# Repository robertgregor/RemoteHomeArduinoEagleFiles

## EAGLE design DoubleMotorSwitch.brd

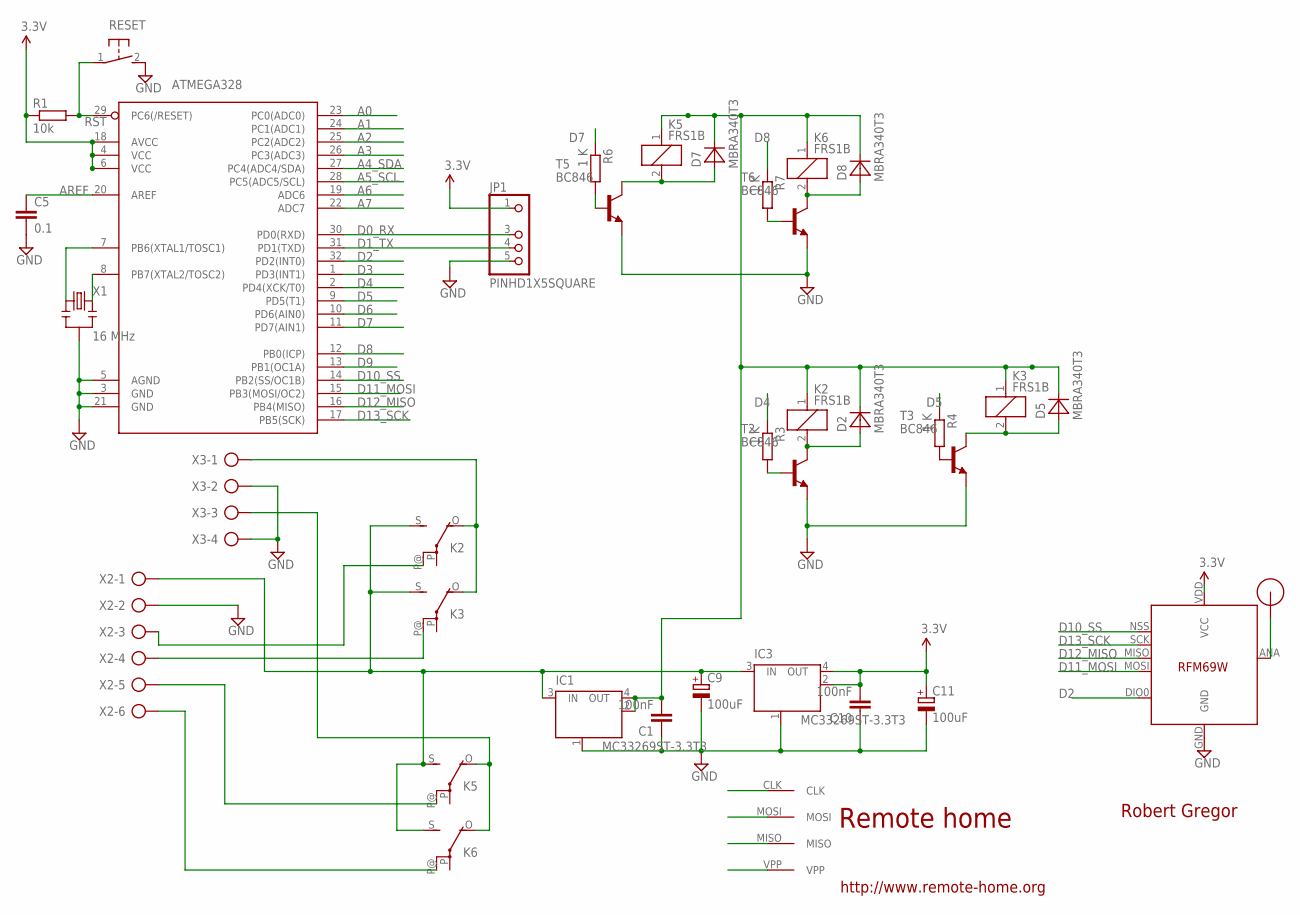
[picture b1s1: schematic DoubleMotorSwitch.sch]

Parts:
ATMEGA328: ATMega-328; TQFP32-08
C1, C10: 100nF; C2012
C5: 0.1; C2012
C9, C11: 100uF; SMC_B
D2, D5, D7, D8: MBRA340T3; SMA
IC1, IC3: MC33269ST-3.3T3; SOT223
JP1: PINHD1X5SQUARE; PINHD1X05-SQUARE
K2, K3, K5, K6: FRS1B
R1: 10k; R2012
R3, R4, R6, R7: 1 K; M2012
RESET: DTSM-3
T2, T3, T5, T6: BC846; SOT23
U$1: RFM12B_ANTENNA; RFM12B-ANTENNA
U$2: AVRHEADERDIP; AVRHEADER
U$5: RFM69; RFM69W-MINPADS
X1: 16 MHz; RESONATOR-SMD
X2: AK500/6
X3: AK500/4

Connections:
5V1: C1.2, D2.C, D5.C, D7.C, D8.C, IC1.2 (OUT), IC1.4 (OUT), K2.1, K3.1, K5.1, K6.1
A0: ATMEGA328.23 (PC0(ADC0))
A1: ATMEGA328.24 (PC1(ADC1))
A2: ATMEGA328.25 (PC2(ADC2))
A3: ATMEGA328.26 (PC3(ADC3))
A4_SDA: ATMEGA328.27 (PC4(ADC4/SDA))
A5_SCL: ATMEGA328.28 (PC5(ADC5/SCL))
A6: ATMEGA328.19 (ADC6)
A7: ATMEGA328.22 (ADC7)
AREF: ATMEGA328.20 (AREF), C5.1
D0_RX: ATMEGA328.30 (PD0(RXD)), JP1.3
D1_TX: ATMEGA328.31 (PD1(TXD)), JP1.4
D2: ATMEGA328.32 (PD2(INT0)), U$5.DIO0
D3: ATMEGA328.1 (PD3(INT1))
D4: ATMEGA328.2 (PD4(XCK/T0)), R3.1
D5: ATMEGA328.9 (PD5(T1)), R4.1
D6: ATMEGA328.10 (PD6(AIN0))
D7: ATMEGA328.11 (PD7(AIN1)), R6.1
D8: ATMEGA328.12 (PB0(ICP)), R7.1
D9: ATMEGA328.13 (PB1(OC1A))
D10_SS: ATMEGA328.14 (PB2(SS/OC1B)), U$5.NSS (SEL)
D11_MOSI: ATMEGA328.15 (PB3(MOSI/OC2)), U$2.MOSI, U$5.MOSI
D12_MISO: ATMEGA328.16 (PB4(MISO)), U$2.MISO, U$5.MISO
D13_SCK: ATMEGA328.17 (PB5(SCK)), U$2.CLK, U$5.SCK
GND: ATMEGA328.3 (GND), ATMEGA328.5 (AGND), ATMEGA328.21 (GND), C1.1, C5.2, C9.-, C10.1, C11.-, IC1.1 (GND/ADJ), IC3.1 (GND/ADJ), JP1.5, RESET.2, T2.2 (E), T3.2 (E), T5.2 (E), T6.2 (E), U$5.GND, X1.2, X2.2, X3.2, X3.4
unnamed: ATMEGA328.7 (PB6(XTAL1/TOSC1)), X1.1
unnamed: U$1.P$1, U$5.ANA (ANT)
unnamed: D2.A, K2.2, T2.3 (C)
unnamed: R3.2, T2.1 (B)
unnamed: K2.P@, X2.3
unnamed: K2.O, K3.O, X3.1
unnamed: K3.P@, X2.4
unnamed: K5.O, K6.O, X3.3
unnamed: C9.+, IC1.3 (IN), IC3.3 (IN), K2.S, K3.S, K5.S, K6.S, X2.1
unnamed: K5.P@, X2.5
unnamed: K6.P@, X2.6
unnamed: ATMEGA328.8 (PB7(XTAL2/TOSC2)), X1.3
unnamed: D5.A, K3.2, T3.3 (C)
unnamed: R4.2, T3.1 (B)
unnamed: D7.A, K5.2, T5.3 (C)
unnamed: R6.2, T5.1 (B)
unnamed: D8.A, K6.2, T6.3 (C)
unnamed: R7.2, T6.1 (B)
RST: ATMEGA328.29 (PC6(/RESET)), R1.2, RESET.1, U$2.VPP
VCC: ATMEGA328.4 (VCC), ATMEGA328.6 (VCC), ATMEGA328.18 (AVCC), C10.2, C11.+, IC3.2 (OUT), IC3.4 (OUT), JP1.1, R1.1, U$5.VDD (VCC)

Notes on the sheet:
Remote home
Robert Gregor
http://www.remote-home.org

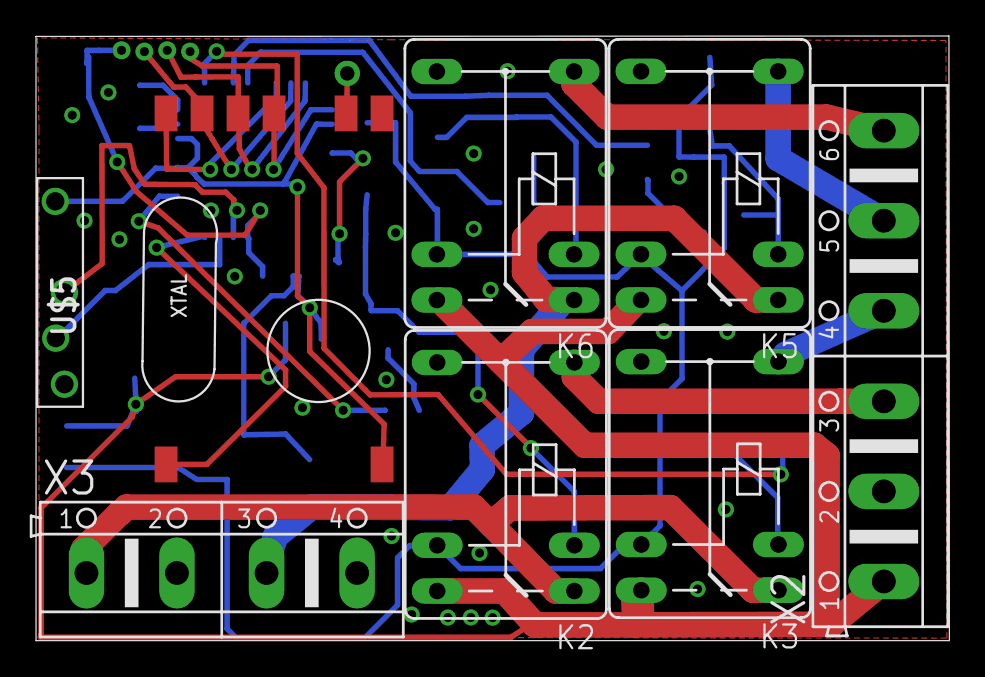
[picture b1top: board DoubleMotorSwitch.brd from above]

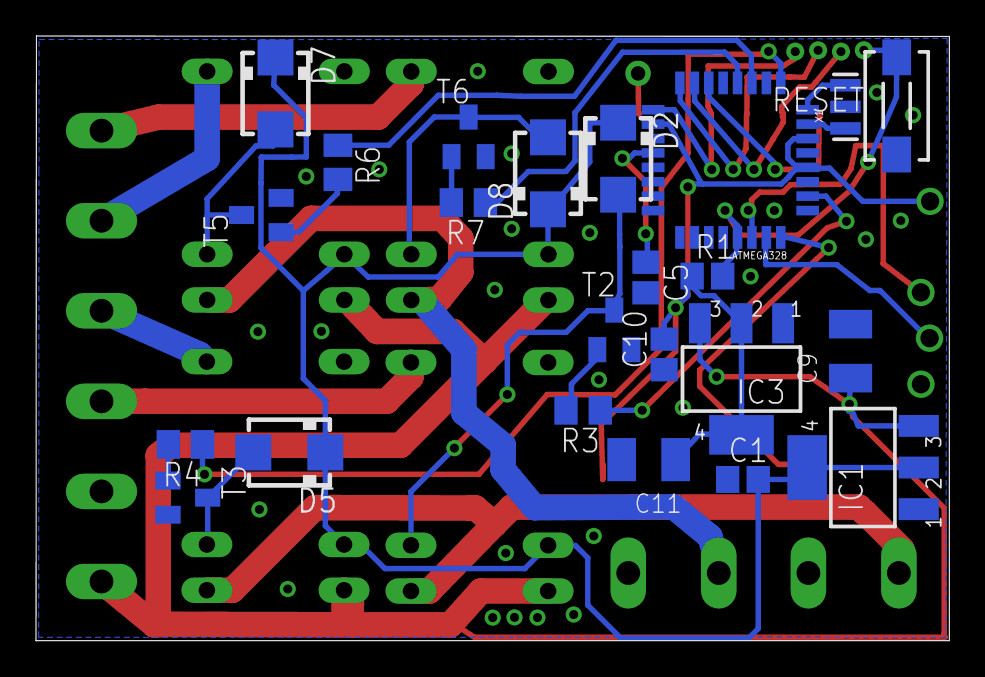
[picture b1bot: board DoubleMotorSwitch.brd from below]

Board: 2 copper layers, 50.7 x 33.6 mm, 33 parts (23 on the bottom side), 34 nets.

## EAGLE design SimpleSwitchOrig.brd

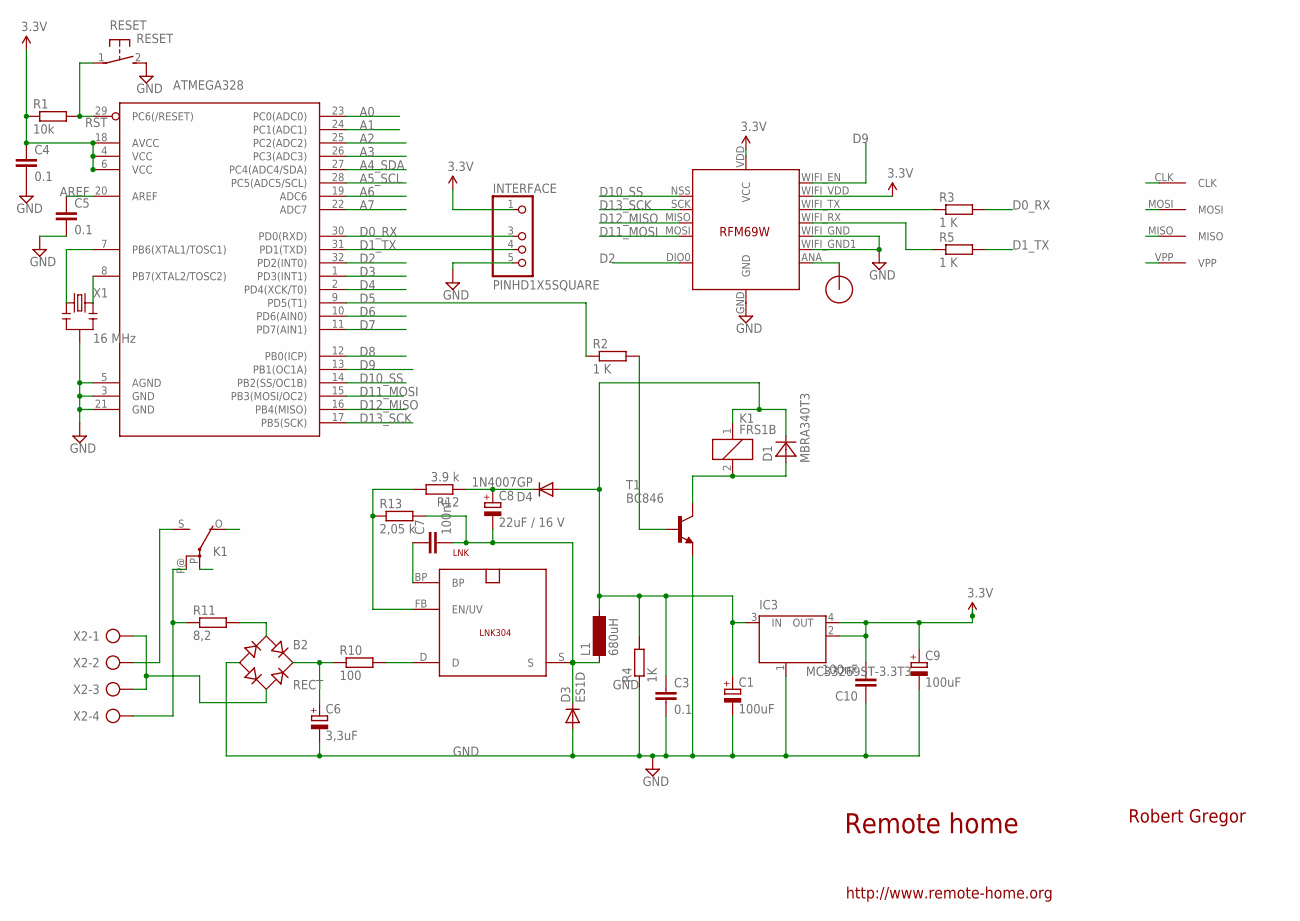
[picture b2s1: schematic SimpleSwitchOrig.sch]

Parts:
ATMEGA328: ATMega-328; TQFP32-08
B2: RECT; TO-269AA
C1, C9: 100uF; SMC_B
C3, C4, C5: 0.1; C2012
C6: 3,3uF; E5-10,5
C7, C10: 100nF; C2012
C8: 22uF / 16 V; SMC_C
D1: MBRA340T3; SMA
D3: ES1D; DO214AC
D4: 1N4007GP; DO214AA
IC3: MC33269ST-3.3T3; SOT223
INTERFACE: PINHD1X5SQUARE; PINHD1X05-SQUARE
K1: FRS1B
L1: 680uH; BS11
LNK: LNK304; SO-8C
R1: 10k; R2012
R2, R3, R5: 1 K; M2012
R4: 1K; M2012
R10: 100; R2512W
R11: 8,2; 0411/12
R12: 3.9 k; M2012
R13: 2,05 k; M2012
RESET: RESET; DTSM-3
RFM69: RFM69-ESP03; RFM69W-ESP03
T1: BC846; SOT23
U$1: RFM12B_ANTENNA; RFM12B-ANTENNA
U$2: AVRHEADERDIP; AVRHEADER
X1: 16 MHz; RESONATOR-SMD
X2: AK500/4

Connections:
5V: C1.+, C3.1, D1.C, D4.A, IC3.3 (IN), K1.1, L1.2, R4.2
A0: ATMEGA328.23 (PC0(ADC0))
A1: ATMEGA328.24 (PC1(ADC1))
A2: ATMEGA328.25 (PC2(ADC2))
A3: ATMEGA328.26 (PC3(ADC3))
A4_SDA: ATMEGA328.27 (PC4(ADC4/SDA))
A5_SCL: ATMEGA328.28 (PC5(ADC5/SCL))
A6: ATMEGA328.19 (ADC6)
A7: ATMEGA328.22 (ADC7)
AREF: ATMEGA328.20 (AREF), C5.1
D0_RX: ATMEGA328.30 (PD0(RXD)), INTERFACE.3, R3.2
D1_TX: ATMEGA328.31 (PD1(TXD)), INTERFACE.4, R5.2
D2: ATMEGA328.32 (PD2(INT0)), RFM69.DIO0
D3: ATMEGA328.1 (PD3(INT1))
D4: ATMEGA328.2 (PD4(XCK/T0))
D5: ATMEGA328.9 (PD5(T1)), R2.1
D6: ATMEGA328.10 (PD6(AIN0))
D7: ATMEGA328.11 (PD7(AIN1))
D8: ATMEGA328.12 (PB0(ICP))
D9: ATMEGA328.13 (PB1(OC1A)), RFM69.WIFI_EN
D10_SS: ATMEGA328.14 (PB2(SS/OC1B)), RFM69.NSS (SEL)
D11_MOSI: ATMEGA328.15 (PB3(MOSI/OC2)), RFM69.MOSI, U$2.MOSI
D12_MISO: ATMEGA328.16 (PB4(MISO)), RFM69.MISO, U$2.MISO
D13_SCK: ATMEGA328.17 (PB5(SCK)), RFM69.SCK, U$2.CLK
FB: LNK.FB (EN/UV), R12.2, R13.1
GND: ATMEGA328.3 (GND), ATMEGA328.5 (AGND), ATMEGA328.21 (GND), B2.-, C1.-, C3.2, C4.2, C5.2, C6.-, C9.-, C10.1, D3.A, IC3.1 (GND/ADJ), INTERFACE.5, R4.1, RESET.2, RFM69.GND, RFM69.WIFI_GND, RFM69.WIFI_GND1, T1.2 (E), X1.2
unnamed: ATMEGA328.7 (PB6(XTAL1/TOSC1)), X1.1
unnamed: R2.2, T1.1 (B)
unnamed: RFM69.ANA (ANT), U$1.P$1
unnamed: D1.A, K1.2, T1.3 (C)
unnamed: K1.S, X2.2
unnamed: K1.P@, R11.1, X2.4
unnamed: B2.AC2, X2.1, X2.3
unnamed: R3.1, RFM69.WIFI_TX
unnamed: R5.1, RFM69.WIFI_RX
unnamed: LNK.D, R10.2
unnamed: B2.+, C6.+, R10.1
unnamed: B2.AC1, R11.2
unnamed: C7.1, LNK.BP
unnamed: C8.+, D4.C, R12.1
unnamed: ATMEGA328.8 (PB7(XTAL2/TOSC2)), X1.3
RST: ATMEGA328.29 (PC6(/RESET)), R1.2, RESET.1, U$2.VPP
S: C7.2, C8.-, D3.C, L1.1, LNK.S, R13.2
VCC: ATMEGA328.4 (VCC), ATMEGA328.6 (VCC), ATMEGA328.18 (AVCC), C4.1, C9.+, C10.2, IC3.2 (OUT), IC3.4 (OUT), INTERFACE.1, R1.1, RFM69.VDD (VCC), RFM69.WIFI_VDD

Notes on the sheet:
Remote home
Robert Gregor
http://www.remote-home.org

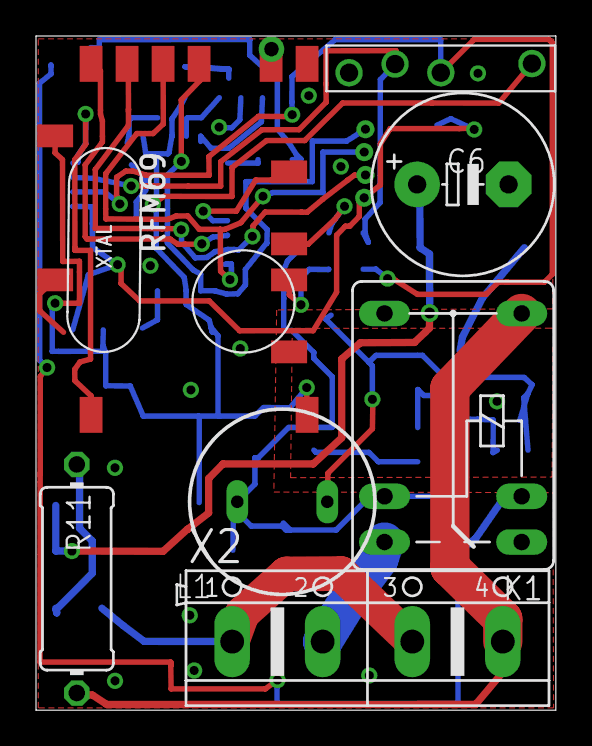
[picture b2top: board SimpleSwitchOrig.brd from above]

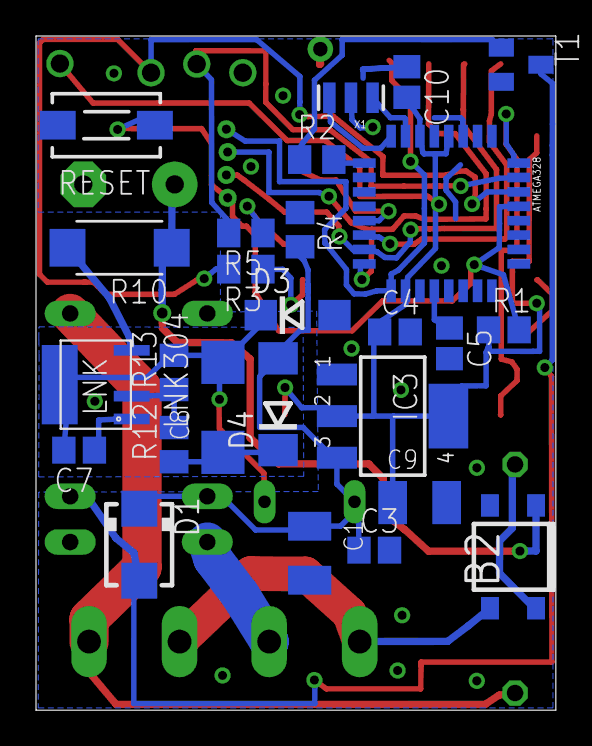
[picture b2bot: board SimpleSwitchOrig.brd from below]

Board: 2 copper layers, 28.9 x 37.5 mm, 35 parts (26 on the bottom side), 31 nets.

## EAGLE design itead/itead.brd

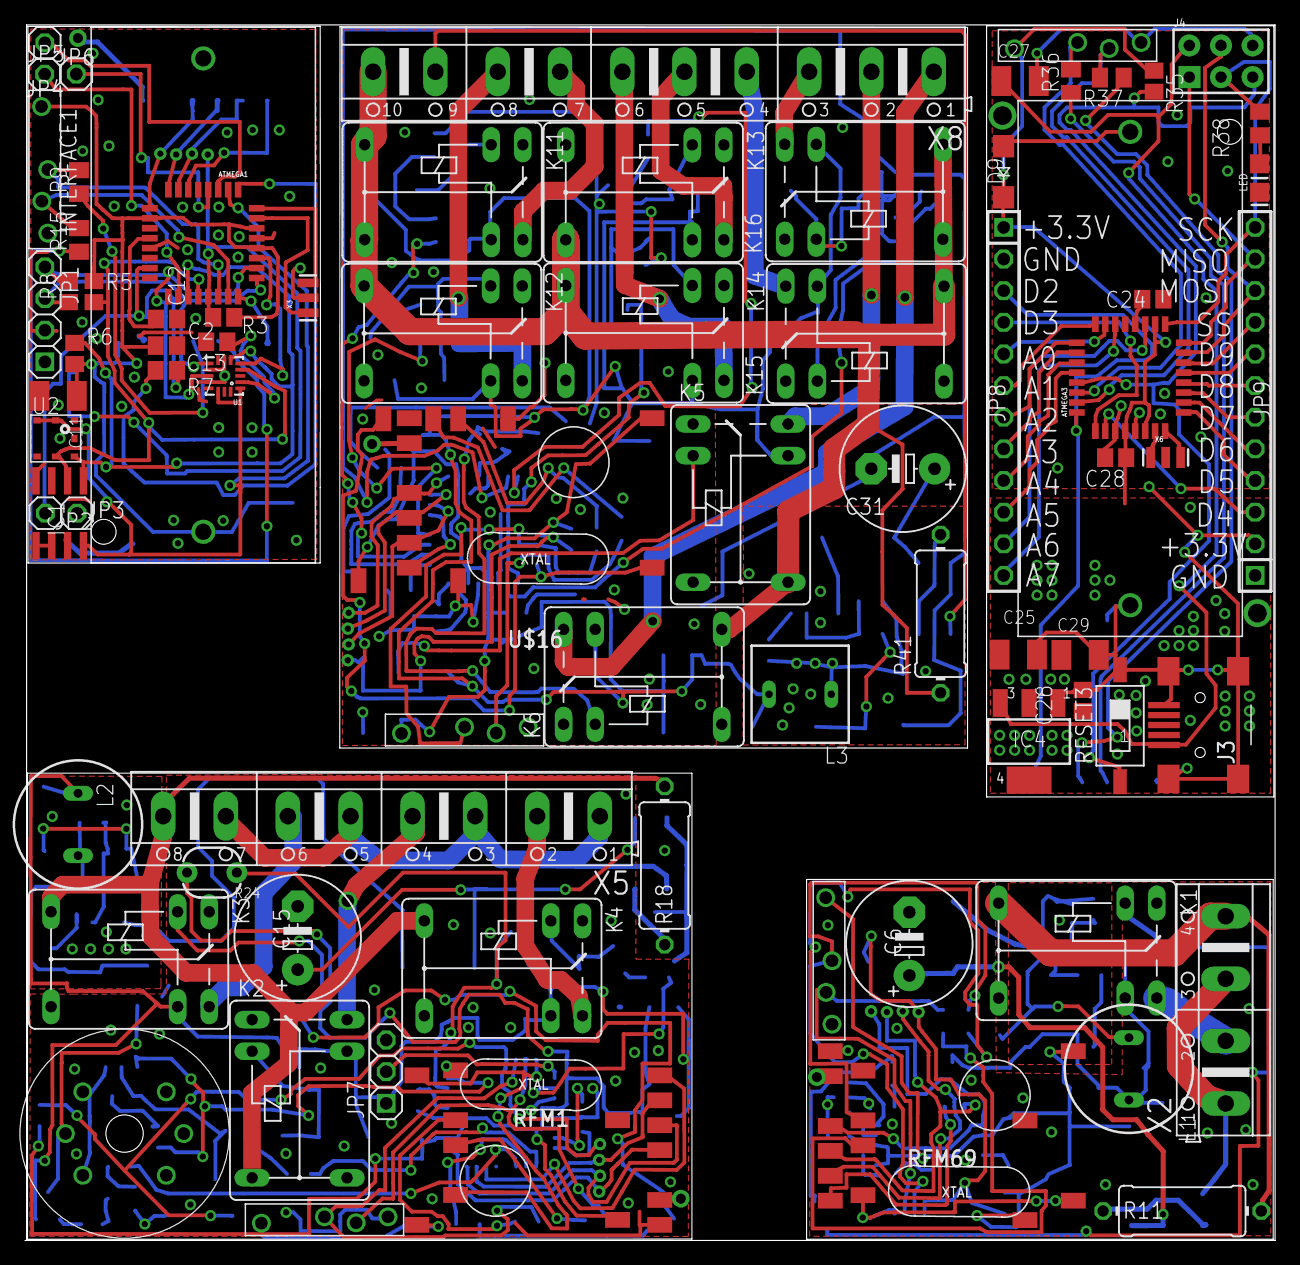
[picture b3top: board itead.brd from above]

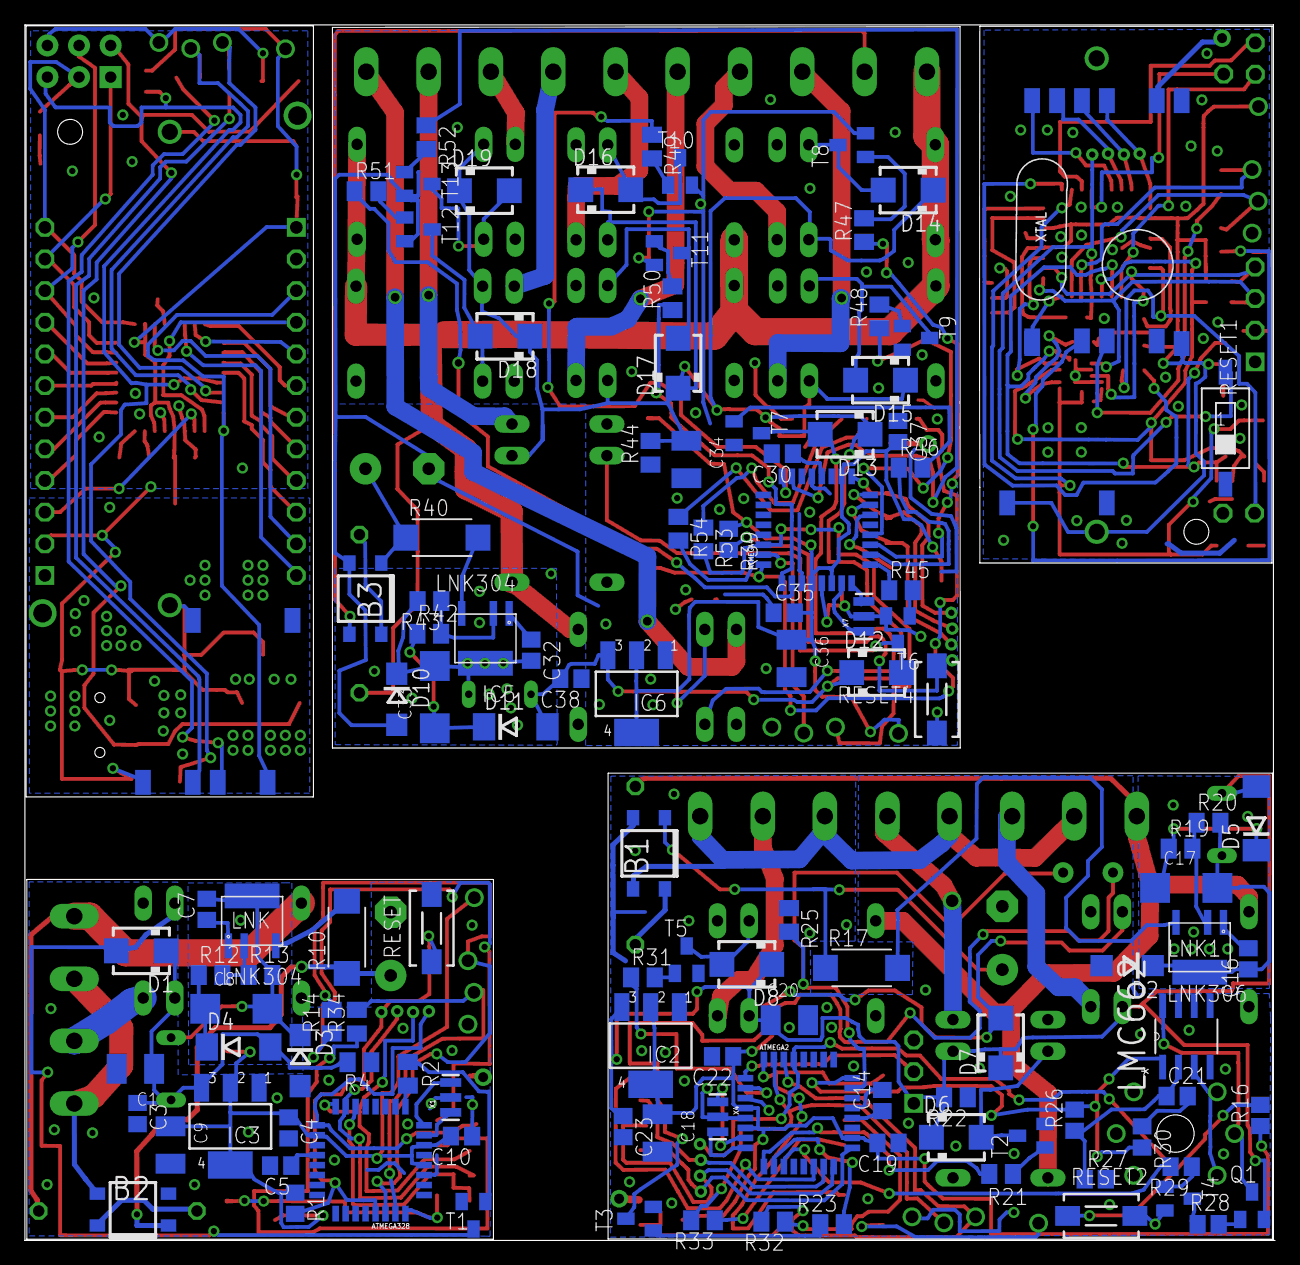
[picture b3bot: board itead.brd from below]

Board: 2 copper layers, 100.2 x 97.6 mm, 209 parts (119 on the bottom side), 197 nets.

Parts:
ATMEGA1, ATMEGA2, ATMEGA3, ATMEGA4, ATMEGA328: ATMega-328; TQFP32-08
B1, B2: RECT; TO-269AA
B3: RECTIFIER; TO-269AA
C1, C9, C11, C18, C20, C25, C27, C29, C34, C36: 100uF; SMC_B
C2, C7, C10, C13, C14, C16, C19, C21, C22, C23, C26, C32, C35, C37, C38: 100nF; C2012
C3, C4, C5, C12, C24, C28, C30: 0.1; C2012
C6, C15, C31: 3,3uF; E5-10,5
C8, C17, C33: 22uF / 16 V; SMC_C
D1, D6, D7, D8, D12, D13, D14, D15, D16, D17, D18, D19: MBRA340T3; SMA
D2, D3, D10: ES1D; DO214AC
D4, D5, D11: 1N4007GP; DO214AA
D9: GF1; SMA-DO214AC
IC1: LM75AD; SO08
IC2, IC3, IC4, IC6: MC33269ST-3.3T3; SOT223
IC5: LNK304; SO-8C
INTERFACE, INTERFACE1, INTERFACE2, INTERFACE3: PINHD1X5SQUARE; PINHD1X05-SQUARE
J3: USB-MINI-B%C; USB-MINI-B_2
J4: HEAD3X2
JP1: 1X04-S
JP2, JP3, JP4, JP5, JP6: 1X01
JP7: 1X03-S
JP8, JP9: 1X12
JP10: PINHD1X5SQUARE; PINHD1X05-SQUARE
K1, K2, K3, K4, K5, K6, K11, K12, K13, K14, K15, K16: FRS1B
L1, L2: 680uH; BS11
L3: 680uH; SD8
LED: L_AMBER; LED0805
LMC662: LMV722IDR; SOIC127P600X175-8N
LNK: LNK304; SO-8C
LNK1: LNK306; SO-8C
Q1: BC327SMD; SOT23-BEC
R1, R3, R5, R6, R7, R8, R16, R26, R28, R35, R39: 10k; R2012
R2, R9, R14, R15, R21, R23, R31, R32, R33, R34, R36, R37, R45, R46, R47, R48, R49, R50, R51, R52, R53, R54: 1 K; M2012
R4, R22, R44: 1K; M2012
R10, R17, R40: 100; R2512W
R11, R18, R41: 8,2; 0411/12
R12, R42: 3.9 k; M2012
R13, R20, R43: 2,05 k; M2012
R19: 5.1 k; M2012
R24: PHOTOCELLPTH; PHOTOCELL
R25: 10 K; M2012
R27: 2k; R2012
R29, R30: 1k; R2012
R38: 220; M2012
RESET, RESET2: RESET; DTSM-3
RESET1, RESET3: SMS-001
RESET4: DTSM-3
RFM1, RFM69: RFM69W
T1, T2, T3, T4, T5, T6, T7, T8, T9, T10, T11, T12, T13: BC846; SOT23
U1: MMA8452Q; QFN-16_0.5MM
U2: BMP180
U$1, U$3, U$8, U$15: RFM12B_ANTENNA; RFM12B-ANTENNA
U$2, U$4, U$10, U$17: AVRHEADERDIP; AVRHEADER
U$5, U$13: BATT-CR123A; KEYSTONE-2/3A
U$6: RFM69W
U$7, U$9, U$12, U$14, U$18: ESP03
U$11: METHANE_SENSOR; MQ-3
U$16: RFM69; RFM69W-MINPADS
X1, X3, X4, X6, X7: 16 MHz; RESONATOR-SMD
X2: AK500/4
X5: AK500/8
X8: AK500/10

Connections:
5V1: C27.+, IC4.3, J3.5, J4.2
5V2: C1.+, C3.1, D1.C, D4.A, IC3.3, K1.1, L1.2, R4.2
5V3: C34.+, C38.2, D11.A, D12.C, D13.C, D14.C, D15.C, D16.C, D17.C, D18.C, D19.C, IC6.3, K5.1, K6.1, K11.1, K12.1, K13.1, K14.1, K15.1, K16.1, L3.2, R44.2
6V: C20.+, C23.1, D5.A, D6.C, D7.C, D8.C, IC2.3, JP7.1, K2.1, K3.1, K4.1, L2.2, Q1.E, R22.2
A4_SDA1: ATMEGA1.27, IC1.1, R6.1, U1.6, U2.6
A4_SDA3: ATMEGA3.27, JP8.9
A5_SCL1: ATMEGA1.28, IC1.2, R5.1, U1.4, U2.5
A5_SCL3: ATMEGA3.28, JP8.10
A8: ATMEGA1.26, JP4.1
A11: ATMEGA1.23, JP2.1, R7.2
A16: ATMEGA2.24, LMC662.1, R26.2, R30.2
A17: ATMEGA2.23, R24.2, R25.2
A18: ATMEGA3.22, JP8.12
A19: ATMEGA3.19, JP8.11
A20: ATMEGA3.26, JP8.8
A21: ATMEGA3.25, JP8.7
A22: ATMEGA3.24, JP8.6
A23: ATMEGA3.23, JP8.5
A28: ATMEGA4.24, R49.1
A29: ATMEGA4.23, R52.1
AREF1: ATMEGA1.20, C12.1
AREF2: ATMEGA2.20, C14.1
AREF3: ATMEGA328.20, C5.1
AREF4: ATMEGA3.20, C24.1
AREF5: ATMEGA4.20, C30.1
D0_RX1: ATMEGA1.30, INTERFACE1.3, R9.2
D0_RX2: ATMEGA2.30, INTERFACE2.3, R32.2
D0_RX3: ATMEGA328.30, INTERFACE.3, R14.2
D0_RX4: ATMEGA3.30, INTERFACE3.3, R36.2
D0_RX5: ATMEGA4.30, JP10.3, R53.2
D1_TX1: ATMEGA1.31, INTERFACE1.4, R15.2
D1_TX2: ATMEGA2.31, INTERFACE2.4, R33.2
D1_TX3: ATMEGA328.31, INTERFACE.4, R34.2
D1_TX4: ATMEGA3.31, INTERFACE3.4, R37.2
D1_TX5: ATMEGA4.31, JP10.4, R54.2
D4: ATMEGA328.9, R2.1
D10: ATMEGA1.12, JP6.1
D10_SS1: ATMEGA1.14, U$6.NSS
D10_SS2: ATMEGA2.14, RFM1.NSS
D10_SS3: ATMEGA328.14, RFM69.NSS
D10_SS4: ATMEGA3.14, JP9.9
D10_SS5: ATMEGA4.14, U$16.NSS
D11: ATMEGA1.11, JP5.1
D11_MOSI1: ATMEGA1.15, U$4.MOSI, U$6.MOSI
D11_MOSI2: ATMEGA2.15, RFM1.MOSI, U$10.MOSI
D11_MOSI3: ATMEGA328.15, RFM69.MOSI, U$2.MOSI
D11_MOSI4: ATMEGA3.15, J4.4, JP9.10
D11_MOSI5: ATMEGA4.15, U$16.MOSI, U$17.MOSI
D12: ATMEGA1.10, IC1.8, U1.1, U1.14, U2.2, U2.3
D12_MISO1: ATMEGA1.16, U$4.MISO, U$6.MISO
D12_MISO2: ATMEGA2.16, RFM1.MISO, U$10.MISO
D12_MISO3: ATMEGA328.16, RFM69.MISO, U$2.MISO
D12_MISO4: ATMEGA3.16, J4.1, JP9.11
D12_MISO5: ATMEGA4.16, U$16.MISO, U$17.MISO
D13: ATMEGA1.9, R7.1
D13_SCK1: ATMEGA1.17, U$4.CLK, U$6.SCK
D13_SCK2: ATMEGA2.17, RFM1.SCK, U$10.CLK
D13_SCK3: ATMEGA328.17, RFM69.SCK, U$2.CLK
D13_SCK4: ATMEGA3.17, J4.3, JP9.12, R38.1
D13_SCK5: ATMEGA4.17, U$16.SCK, U$17.CLK
D14: ATMEGA1.2, JP1.4, R8.2, U1.11
D15: ATMEGA1.1, JP1.3, R8.1, U1.9
D16: ATMEGA1.32, U$6.DIO0, U$7.WIFI_EN
D19: ATMEGA2.11, R29.2
D20: ATMEGA2.10, R23.1
D21: ATMEGA2.9, R21.1
D22: ATMEGA2.2, R31.1
D23: ATMEGA2.1, JP7.2
D24: ATMEGA2.32, RFM1.DIO0, U$12.WIFI_EN
D27: ATMEGA328.32, RFM69.DIO0, U$9.WIFI_EN
D28: ATMEGA3.13, JP9.8
D29: ATMEGA3.12, JP9.7
D30: ATMEGA3.11, JP9.6
D31: ATMEGA3.10, JP9.5
D32: ATMEGA3.9, JP9.4
D33: ATMEGA3.2, JP9.3
D34: ATMEGA3.1, JP8.4
D35: ATMEGA3.32, JP8.3, U$14.WIFI_EN
D37: ATMEGA4.12, R48.1
D38: ATMEGA4.11, R47.1
D39: ATMEGA4.10, R46.1
D40: ATMEGA4.2, R51.1
D41: ATMEGA4.1, R50.1
D42: ATMEGA4.32, U$16.DIO0, U$18.WIFI_EN
D43: ATMEGA4.9, R45.1
FB1: LNK1.FB, R19.2, R20.1
FB2: LNK.FB, R12.2, R13.1
GND1: ATMEGA1.3, ATMEGA1.5, ATMEGA1.21, C2.2, C11.-, C12.2, C13.2, IC1.4, IC1.5, IC1.6, IC1.7, INTERFACE1.5, JP1.1, JP1.2, JP3.1, RESET1.2, U1.5, U1.7, U1.10, U1.12, U2.7, U$5.-VE, U$6.GND, U$7.WIFI_GND, U$7.WIFI_GPIO15, X3.2
GND2: ATMEGA2.3, ATMEGA2.5, ATMEGA2.21, B1.-, C14.2, C15.-, C18.-, C19.1, C20.-, C22.2, C23.2, D2.A, IC2.1, INTERFACE2.5, JP7.3, LMC662.4, R22.1, R25.1, R27.2, RESET2.2, RFM1.GND, T2.2, T3.2, T4.2, T5.2, U$11.A1, U$11.A2, U$11.HA, U$12.WIFI_GND, U$12.WIFI_GPIO15, X4.2
GND3: ATMEGA328.3, ATMEGA328.5, ATMEGA328.21, B2.-, C1.-, C3.2, C4.2, C5.2, C6.-, C9.-, C10.1, D3.A, IC3.1, INTERFACE.5, R4.1, RESET.2, RFM69.GND, T1.2, U$9.WIFI_GND, U$9.WIFI_GPIO15, X1.2
GND4: ATMEGA3.3, ATMEGA3.5, ATMEGA3.21, C24.2, C25.-, C26.1, C27.-, C28.2, C29.-, IC4.1, INTERFACE3.5, J3.1, J3.6, J3.7, J3.8, J3.9, J4.6, JP8.2, JP9.2, LED.1, RESET3.2, U$13.-VE, U$14.WIFI_GND, U$14.WIFI_GPIO15, X6.2
GND5: ATMEGA4.3, ATMEGA4.5, ATMEGA4.21, B3.-, C30.2, C31.-, C34.-, C35.1, C36.-, C37.1, C38.1, D10.A, IC6.1, JP10.5, R44.1, RESET4.2, T6.2, T7.2, T8.2, T9.2, T10.2, T11.2, T12.2, T13.2, U$16.GND, U$18.WIFI_GND, U$18.WIFI_GPIO15, X7.2
unnamed: ATMEGA328.7, X1.1
unnamed: ATMEGA328.8, X1.3
unnamed: ATMEGA1.7, X3.1
unnamed: ATMEGA1.8, X3.3
unnamed: U$3.P$1, U$6.ANA
unnamed: RFM69.ANA, U$1.P$1
unnamed: C13.1, U1.2
unnamed: R9.1, U$7.WIFI_TX
unnamed: R15.1, U$7.WIFI_RX
unnamed: ATMEGA2.7, X4.1
unnamed: ATMEGA2.8, X4.3
unnamed: RFM1.ANA, U$8.P$1
unnamed: K2.P@, K3.P@, K4.P@, R18.1, X5.8
unnamed: B1.AC2, X5.1, X5.3, X5.5, X5.7
unnamed: K3.S, X5.6
unnamed: LNK1.D, R17.2
unnamed: B1.+, C15.+, R17.1
unnamed: B1.AC1, R18.2
unnamed: C16.1, LNK1.BP
unnamed: C17.+, D5.C, R19.1
unnamed: D6.A, K2.2, T2.3
unnamed: R21.2, T2.1
unnamed: D7.A, K3.2, T3.3
unnamed: R23.2, T3.1
unnamed: K2.S, X5.4
unnamed: LMC662.3, U$11.B1, U$11.B2
unnamed: LMC662.8, Q1.C, U$11.HB
unnamed: R29.1, T4.1
unnamed: R28.2, T4.3
unnamed: Q1.B, R28.1
unnamed: C21.1, LMC662.2, R26.1, R27.1
unnamed: C21.2, R30.1
unnamed: K4.S, X5.2
unnamed: D8.A, K4.2, T5.3
unnamed: R31.2, T5.1
unnamed: R32.1, U$12.WIFI_TX
unnamed: R33.1, U$12.WIFI_RX
unnamed: ATMEGA3.7, X6.1
unnamed: ATMEGA3.8, X6.3
unnamed: K1.P@, R11.1, X2.4
unnamed: B2.AC2, X2.1, X2.3
unnamed: K1.S, X2.2
unnamed: LNK.D, R10.2
unnamed: B2.+, C6.+, R10.1
unnamed: B2.AC1, R11.2
unnamed: C7.1, LNK.BP
unnamed: C8.+, D4.C, R12.1
unnamed: D1.A, K1.2, T1.3
unnamed: R2.2, T1.1
unnamed: R14.1, U$9.WIFI_TX
unnamed: R34.1, U$9.WIFI_RX
unnamed: R36.1, U$14.WIFI_TX
unnamed: R37.1, U$14.WIFI_RX
unnamed: D9.A, U$13.+VE
unnamed: LED.2, R38.2
unnamed: ATMEGA4.7, X7.1
unnamed: ATMEGA4.8, X7.3
unnamed: U$15.P$1, U$16.ANA
unnamed: B3.AC2, X8.9
unnamed: K5.S, X8.2
unnamed: IC5.D, R40.2
unnamed: B3.+, C31.+, R40.1
unnamed: B3.AC1, R41.2
unnamed: C32.1, IC5.BP
unnamed: C33.+, D11.C, R42.1
unnamed: D12.A, K5.2, T6.3
unnamed: R45.2, T6.1
unnamed: D13.A, K6.2, T7.3
unnamed: R46.2, T7.1
unnamed: D14.A, K11.2, T8.3
unnamed: R47.2, T8.1
unnamed: D15.A, K12.2, T9.3
unnamed: R48.2, T9.1
unnamed: D16.A, K13.2, T10.3
unnamed: R49.2, T10.1
unnamed: D17.A, K14.2, T11.3
unnamed: R50.2, T11.1
unnamed: D18.A, K15.2, T12.3
unnamed: R51.2, T12.1
unnamed: D19.A, K16.2, T13.3
unnamed: R52.2, T13.1
unnamed: K5.P, K6.P, K11.P, K11.P@, K12.P@, K13.P, K14.P@, K15.P, K16.P, K16.P@, R41.1, X8.10
unnamed: K16.S, X8.3
unnamed: K13.S, X8.5
unnamed: K14.S, X8.6
unnamed: K15.S, X8.4
unnamed: K12.S, X8.8
unnamed: K11.S, X8.7
unnamed: K6.S, X8.1
unnamed: R53.1, U$18.WIFI_TX
unnamed: R54.1, U$18.WIFI_RX
RST1: ATMEGA1.29, R3.2, RESET1.1, U$4.VPP
RST2: ATMEGA2.29, R16.2, RESET2.1, U$10.VPP
RST3: ATMEGA328.29, R1.2, RESET.1, U$2.VPP
RST4: ATMEGA3.29, J4.5, R35.2, RESET3.1
RST5: ATMEGA4.29, R39.2, RESET4.1, U$17.VPP
S: C7.2, C8.-, D3.C, L1.1, LNK.S, R13.2
S1: C16.2, C17.-, D2.C, L2.1, LNK1.S, R20.2
S3: C32.2, C33.-, D10.C, IC5.S, L3.1, R43.2
VCC1: ATMEGA1.4, ATMEGA1.6, ATMEGA1.18, C2.1, C11.+, INTERFACE1.1, R3.1, R5.2, R6.2, U$5.+VE, U$6.VDD, U$7.WIFI_VDD
VCC2: ATMEGA2.4, ATMEGA2.6, ATMEGA2.18, C18.+, C19.2, C22.1, IC2.2, IC2.4, INTERFACE2.1, R16.1, R24.1, RFM1.VDD, U$12.WIFI_VDD
VCC3: ATMEGA328.4, ATMEGA328.6, ATMEGA328.18, C4.1, C9.+, C10.2, IC3.2, IC3.4, INTERFACE.1, R1.1, RFM69.VDD, U$9.WIFI_VDD
VCC4: ATMEGA3.4, ATMEGA3.6, ATMEGA3.18, C25.+, C26.2, C28.1, C29.+, D9.K, IC4.2, IC4.4, INTERFACE3.1, JP8.1, JP9.1, R35.1, U$14.WIFI_VDD
VCC5: ATMEGA4.4, ATMEGA4.6, ATMEGA4.18, C35.2, C36.+, C37.2, IC6.2, IC6.4, JP10.1, R39.1, U$16.VDD, U$18.WIFI_VDD
XXX: IC5.FB, R42.2, R43.1

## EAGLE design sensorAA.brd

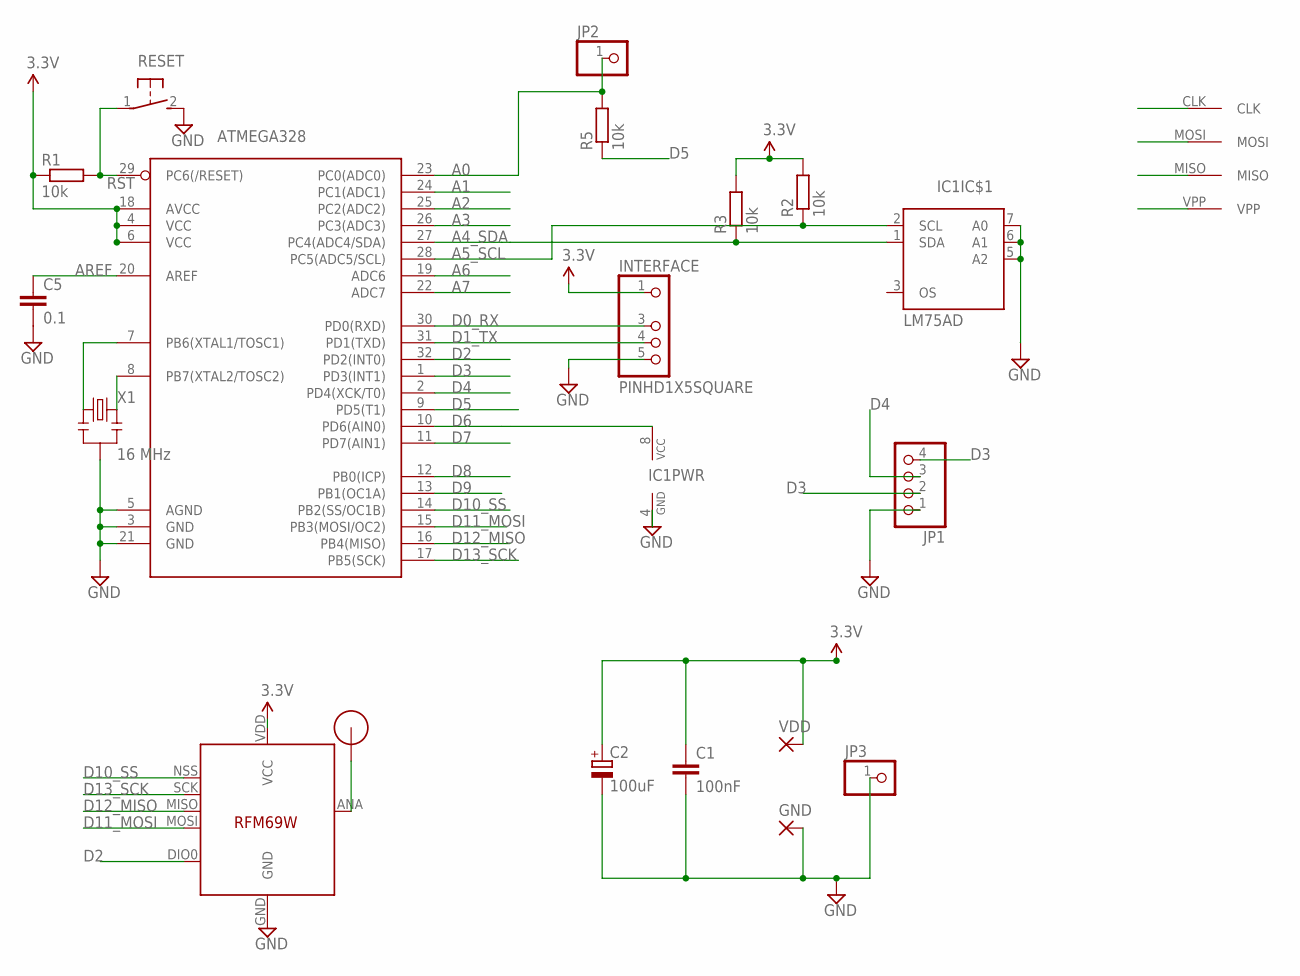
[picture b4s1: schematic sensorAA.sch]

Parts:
ATMEGA328: ATMega-328; TQFP32-08
C1: 100nF; C2012
C2: 100uF; SMC_B
C5: 0.1; C2012
GND: SMD5; SMD2,54-5,08
IC1: LM75AD; SO08
IC4: RFM69; RFM69W-MINPADS
INTERFACE: PINHD1X5SQUARE; PINHD1X05-SQUARE
JP1: PINHD-1X04_2.54-S; 1X04-S
JP2, JP3: PINHD-1X01_2.54; 1X01
R1, R2, R3, R5: 10k; R2012
RESET: DTSM-3
U$1: RFM12B_ANTENNA; RFM12B-ANTENNA
U$2: AVRHEADERDIP; AVRHEADER
VDD: SMD5; SMD2,54-5,08
X1: 16 MHz; RESONATOR-SMD

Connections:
A0: ATMEGA328.23 (PC0(ADC0)), JP2.1, R5.2
A1: ATMEGA328.24 (PC1(ADC1))
A2: ATMEGA328.25 (PC2(ADC2))
A3: ATMEGA328.26 (PC3(ADC3))
A4_SDA: ATMEGA328.27 (PC4(ADC4/SDA)), IC1.1 (SDA), R3.1
A5_SCL: ATMEGA328.28 (PC5(ADC5/SCL)), IC1.2 (SCL), R2.1
A6: ATMEGA328.19 (ADC6)
A7: ATMEGA328.22 (ADC7)
AREF: ATMEGA328.20 (AREF), C5.1
D0_RX: ATMEGA328.30 (PD0(RXD)), INTERFACE.3
D1_TX: ATMEGA328.31 (PD1(TXD)), INTERFACE.4
D2: ATMEGA328.32 (PD2(INT0)), IC4.DIO0
D3: ATMEGA328.1 (PD3(INT1)), JP1.2, JP1.4
D4: ATMEGA328.2 (PD4(XCK/T0)), JP1.3
D5: ATMEGA328.9 (PD5(T1)), R5.1
D6: ATMEGA328.10 (PD6(AIN0)), IC1.8 (VCC)
D7: ATMEGA328.11 (PD7(AIN1))
D8: ATMEGA328.12 (PB0(ICP))
D9: ATMEGA328.13 (PB1(OC1A))
D10_SS: ATMEGA328.14 (PB2(SS/OC1B)), IC4.NSS (SEL)
D11_MOSI: ATMEGA328.15 (PB3(MOSI/OC2)), IC4.MOSI, U$2.MOSI
D12_MISO: ATMEGA328.16 (PB4(MISO)), IC4.MISO, U$2.MISO
D13_SCK: ATMEGA328.17 (PB5(SCK)), IC4.SCK, U$2.CLK
GND: ATMEGA328.3 (GND), ATMEGA328.5 (AGND), ATMEGA328.21 (GND), C1.2, C2.-, C5.2, GND.1, IC1.4 (GND), IC1.5 (A2), IC1.6 (A1), IC1.7 (A0), IC4.GND, INTERFACE.5, JP1.1, JP3.1, RESET.2, X1.2
unnamed: ATMEGA328.7 (PB6(XTAL1/TOSC1)), X1.1
unnamed: IC4.ANA (ANT), U$1.P$1
unnamed: ATMEGA328.8 (PB7(XTAL2/TOSC2)), X1.3
RST: ATMEGA328.29 (PC6(/RESET)), R1.2, RESET.1, U$2.VPP
VCC: ATMEGA328.4 (VCC), ATMEGA328.6 (VCC), ATMEGA328.18 (AVCC), C1.1, C2.+, IC4.VDD (VCC), INTERFACE.1, R1.1, R2.2, R3.2, VDD.1

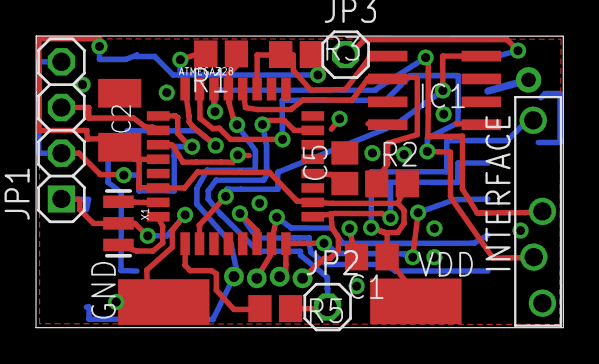
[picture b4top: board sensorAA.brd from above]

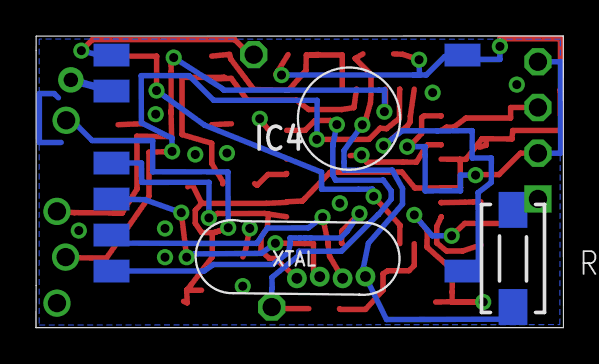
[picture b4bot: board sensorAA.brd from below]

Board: 2 copper layers, 29.3 x 16.2 mm, 20 parts (2 on the bottom side), 21 nets.

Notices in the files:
parts and their libraries:
eagle-library-edeca.net-v5: This is v1 and is licensed under the Creative Commons (Attribution-Non-Commercial-Share Alike 2.0 UK)
SparkFun-Sensors: Licensing: Creative Commons ShareAlike 4.0 International - https://creativecommons.org/licenses/by-sa/4.0
